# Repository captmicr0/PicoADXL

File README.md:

# PicoADXL
 RP2040 + ADXL, but with a commonly found JST-SH 5p 1mm connector used for USB data.

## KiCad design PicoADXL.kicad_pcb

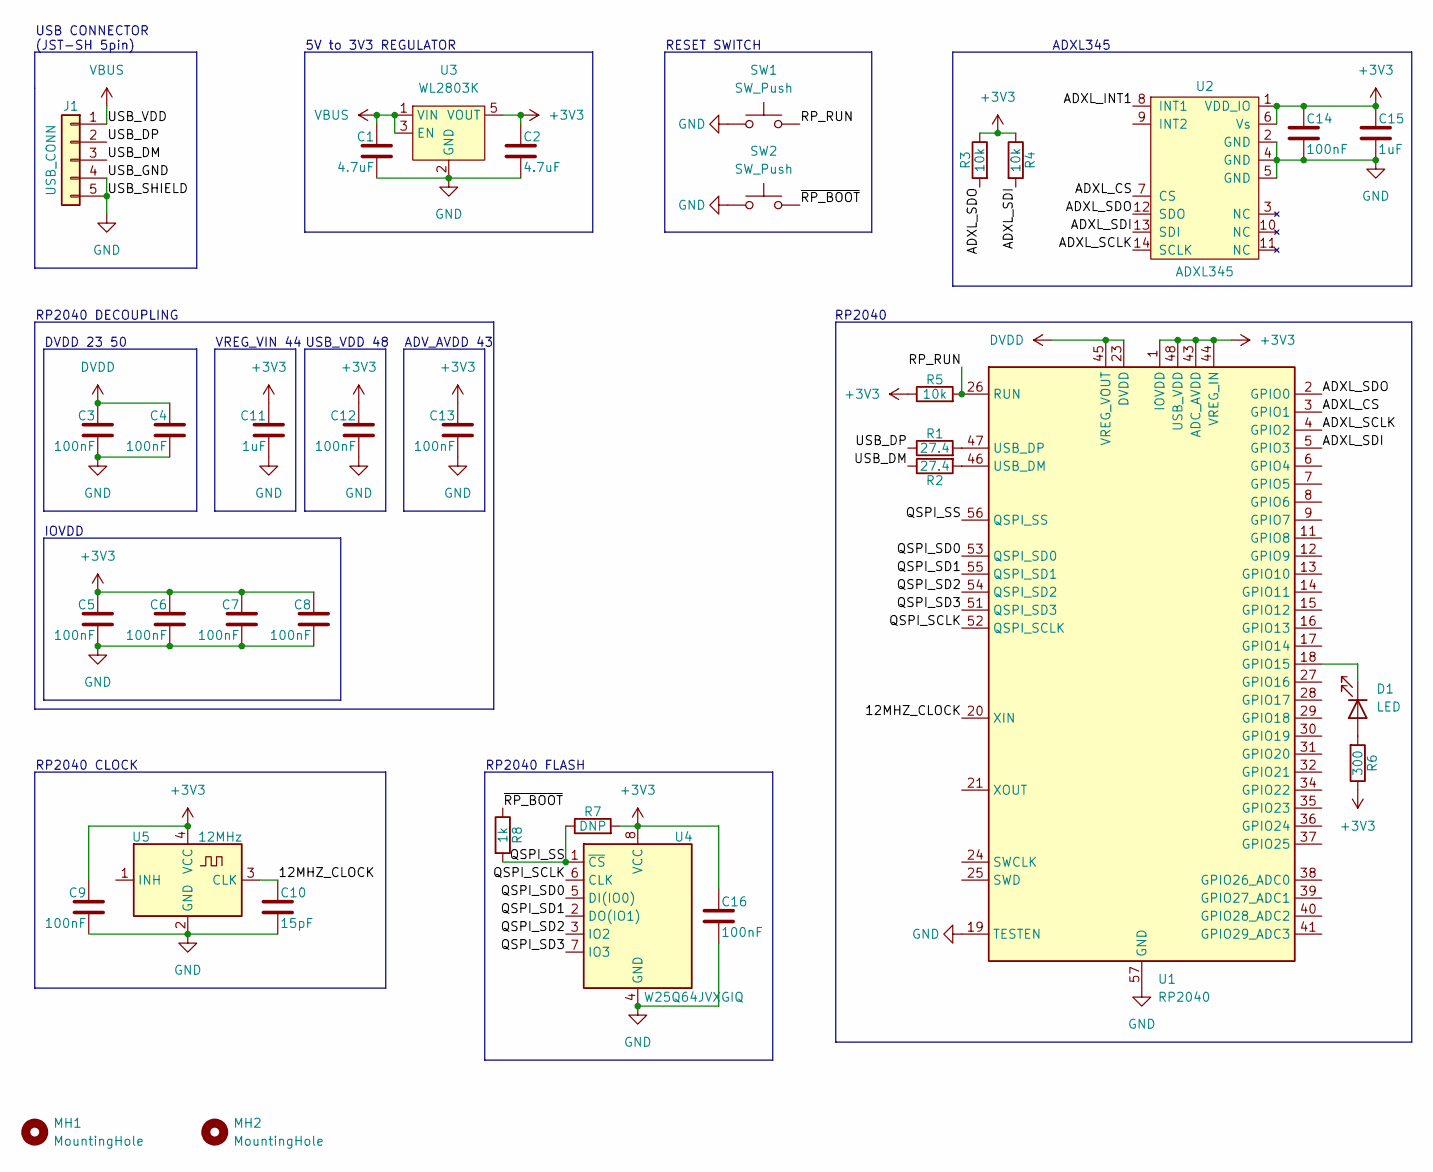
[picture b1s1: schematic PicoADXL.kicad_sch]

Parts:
C1, C2: 4.7uF; C_0603_1608Metric; LCSC# C109456
C3, C4, C5, C6, C7, C8, C9, C12, C13, C14, C16: 100nF; C_0603_1608Metric; LCSC# C14663
C10: 15pF; C_0603_1608Metric; LCSC# C107037
C11, C15: 1uF; C_0603_1608Metric; LCSC# C106214
D1: LED; LED_0603_1608Metric; LCSC# C434421
J1: USB_CONN; JST_SH_SM05B-SRSS-TB_1x05-1MP_P1.00mm_Horizontal; LCSC# C136657
MH1, MH2: MountingHole; MountingHole_2.2mm_M2
R1, R2: 27.4; R_0603_1608Metric; LCSC# C185346
R3, R4, R5: 10k; R_0603_1608Metric; LCSC# C98220
R6: 300; R_0603_1608Metric; LCSC# C114617
R7: DNP; R_0603_1608Metric; LCSC# C98220
R8: 1k; R_0603_1608Metric; LCSC# C22548
SW1, SW2: SW_Push; SW_SPST_B3U-3000P; LCSC# C963349
U1: RP2040; QFN-56-1EP_7x7mm_P0.4mm_EP3.2x3.2mm; LCSC# C2040
U2: ADXL345; ADXL3x5; Farnell 1853935
U3: WL2803K; SOT-89-5; LCSC# C192927
U4: W25Q64JVXGIQ; WSON-8-1EP_4x4mm_P0.8mm_EP2.2x3mm; LCSC# C2940195
U5: 12MHz; Oscillator_SMD_Kyocera_KC2520Z-4Pin_2.5x2.0mm; LCSC# C7425459

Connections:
+3V3: C2.1, C5.1, C6.1, C7.1, C8.1, C9.1, C11.1, C12.1, C13.1, C14.1, C15.1, C16.1, R3.1, R4.1, R5.1, R6.1, R7.2, U1.1 (IOVDD), U1.10 (IOVDD), U1.22 (IOVDD), U1.33 (IOVDD), U1.42 (IOVDD), U1.43 (ADC_AVDD), U1.44 (VREG_IN), U1.48 (USB_VDD), U1.49 (IOVDD), U2.1 (VDD_IO), U2.6 (Vs), U3.5 (VOUT), U4.8 (VCC), U5.4 (VCC)
/12MHZ_CLOCK: C10.1, U1.20 (XIN), U5.3 (CLK)
/ADXL_CS: U1.3 (GPIO1), U2.7 (CS)
/ADXL_INT1: U2.8 (INT1)
/ADXL_SCLK: U1.4 (GPIO2), U2.14 (SCLK)
/ADXL_SDI: R4.2, U1.5 (GPIO3), U2.13 (SDI)
/ADXL_SDO: R3.2, U1.2 (GPIO0), U2.12 (SDO)
/QSPI_SCLK: U1.52 (QSPI_SCLK), U4.6 (CLK)
/QSPI_SD0: U1.53 (QSPI_SD0), U4.5 (DI(IO0))
/QSPI_SD1: U1.55 (QSPI_SD1), U4.2 (DO(IO1))
/QSPI_SD2: U1.54 (QSPI_SD2), U4.3 (IO2)
/QSPI_SD3: U1.51 (QSPI_SD3), U4.7 (IO3)
/QSPI_SS: R7.1, R8.2, U1.56 (QSPI_SS), U4.1 (~CS)
/RP_RUN: R5.2, SW1.2, U1.26 (RUN)
/USB_DM: J1.3, R2.1
/USB_DP: J1.2, R1.1
/~RP_BOOT: R8.1, SW2.2
DVDD: C3.1, C4.1, U1.23 (DVDD), U1.45 (VREG_VOUT), U1.50 (DVDD)
GND: C1.2, C2.2, C3.2, C4.2, C5.2, C6.2, C7.2, C8.2, C9.2, C10.2, C11.2, C12.2, C13.2, C14.2, C15.2, C16.2, J1.4, J1.5, SW1.1, SW2.1, U1.19 (TESTEN), U1.57 (GND), U2.2 (GND), U2.4 (GND), U2.5 (GND), U3.2 (GND), U4.4 (GND), U5.2 (GND)
unnamed: D1.2 (A), R6.2
unnamed: D1.1 (K), U1.18 (GPIO15)
unnamed: R2.2, U1.46 (USB_DM)
unnamed: R1.2, U1.47 (USB_DP)
VBUS: C1.1, J1.1, U3.1 (VIN), U3.3 (EN)

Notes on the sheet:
VREG_VIN 44
RP2040
5V to 3V3 REGULATOR
ADXL345
RP2040 DECOUPLING
RESET SWITCH
USB_VDD 48
DVDD 23 50
USB CONNECTOR (JST-SH 5pin)
RP2040 FLASH
IOVDD
RP2040 CLOCK
ADV_AVDD 43

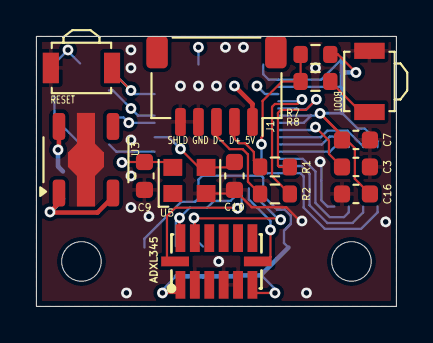
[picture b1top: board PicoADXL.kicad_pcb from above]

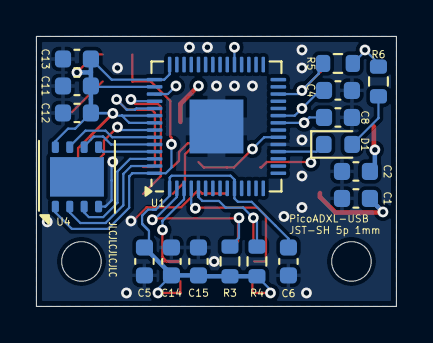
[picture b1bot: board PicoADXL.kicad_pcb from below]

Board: 4 copper layers, 20.0 x 15.0 mm, 35 parts (18 on the bottom side), 23 nets.

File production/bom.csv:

Designator,Footprint,Quantity,Value,LCSC Part #
"C1, C2",0603,2,4.7uF,C109456
C10,0603,1,15pF,C107037
"C11, C15",0603,2,1uF,C106214
"C12, C13, C14, C16, C3, C4, C5, C6, C7, C8, C9",0603,11,100nF,C14663
D1,0603,1,LED,C434421
J1,JST_SH_SM05B-SRSS-TB_1x05-1MP_P1.00mm_Horizontal,1,USB_CONN,C136657
"R1, R2",0603,2,27.4,C185346
"R3, R4, R5",0603,3,10k, C98220
R6,0603,1,300, C114617
R7,0603,1,DNP, C98220
R8,0603,1,1k, C22548
"SW1, SW2",SW_SPST_B3U-3000P,2,SW_Push,C963349
U1,QFN-56-1EP_7x7mm_P0.4mm_EP3.2x3.2mm,1,RP2040,C2040
U2,ADXL3x5,1,ADXL345,C9667
U3,SOT-89-5,1,WL2803K,C192927
U4,WSON-8-1EP_4x4mm_P0.8mm_EP2.2x3mm,1,W25Q64JVXGIQ,C2940195
U5,Oscillator_SMD_Kyocera_KC2520Z-4Pin_2.5x2.0mm,1,12MHz,C7425459

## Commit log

2024-08-14 added lcsc part # field for fab toolkit
